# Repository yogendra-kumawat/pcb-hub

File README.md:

# PCB Hub

A curated collection of custom PCBs designed in **KiCad**, spanning embedded systems, motion control, RF communication, and analog signal generation. Each board was designed from scratch — schematic capture, layout, and fabrication-ready Gerbers — with a focus on clean routing, proper power distribution, and real-world hardware integration.

---

## Projects

| Project | Description | Board Size | Layers |
|---|---|---|---|
| [Flight Controller](#flight-controller) | STM32 + LoRa + IMU flight controller | 91.4 × 69.4 mm | 2 |
| [Function Generator](#function-generator) | STM32-based multi-waveform signal generator | 90.4 × 45.0 mm | 2 |
| [Writing Machine](#writing-machine) | 2-DOF polar arm plotter motor driver board | 56.2 × 26.0 mm | 2 |

## Machines
|Item|Description|
|---|---|
| [Drill Machine](#drill-machine) | Speed-controlled PCB drill with motor driver 
| [Solution Machine](#solution-machine) | Automated liquid dispensing controller 

---

## Tools

- **EDA**: KiCad 10.0
- **Fabrication**: JLCPCB / standard 2-layer FR4, 1.6 mm
- **Design Rules**: 0.2 mm min trace, 0.2 mm min clearance

---

*All KiCad source files (`.kicad_pcb` + `.kicad_sch`) are included in each project's `/kicad` subfolder.*

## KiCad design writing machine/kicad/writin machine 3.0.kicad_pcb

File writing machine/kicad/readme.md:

# KiCad Source — Writing Machine v3.0

This folder contains the complete KiCad project for the writing machine motor driver board.

## Files

| File | Description |
|---|---|
| `writin machine 3.0.kicad_sch` | Full schematic — STC8G1K08A MCU, 3× 2N2219 BJT motor drivers, AMS1117-5.0, UART header, motor output connectors |
| `writin machine 3.0.kicad_pcb` | 2-layer PCB layout — 56.2 × 26.0 mm, FR4 1.6 mm |

## Requirements

- KiCad **10.0** or later
- Custom symbol: `MCU_STC:STC8G1K08A-36I-DFN8` — included in the schematic's embedded library

## Design Notes

- Board thickness: **1.6 mm**

## How to Open

```bash
kicad "writin machine 3.0.kicad_pcb"
kicad "writin machine 3.0.kicad_sch"
```

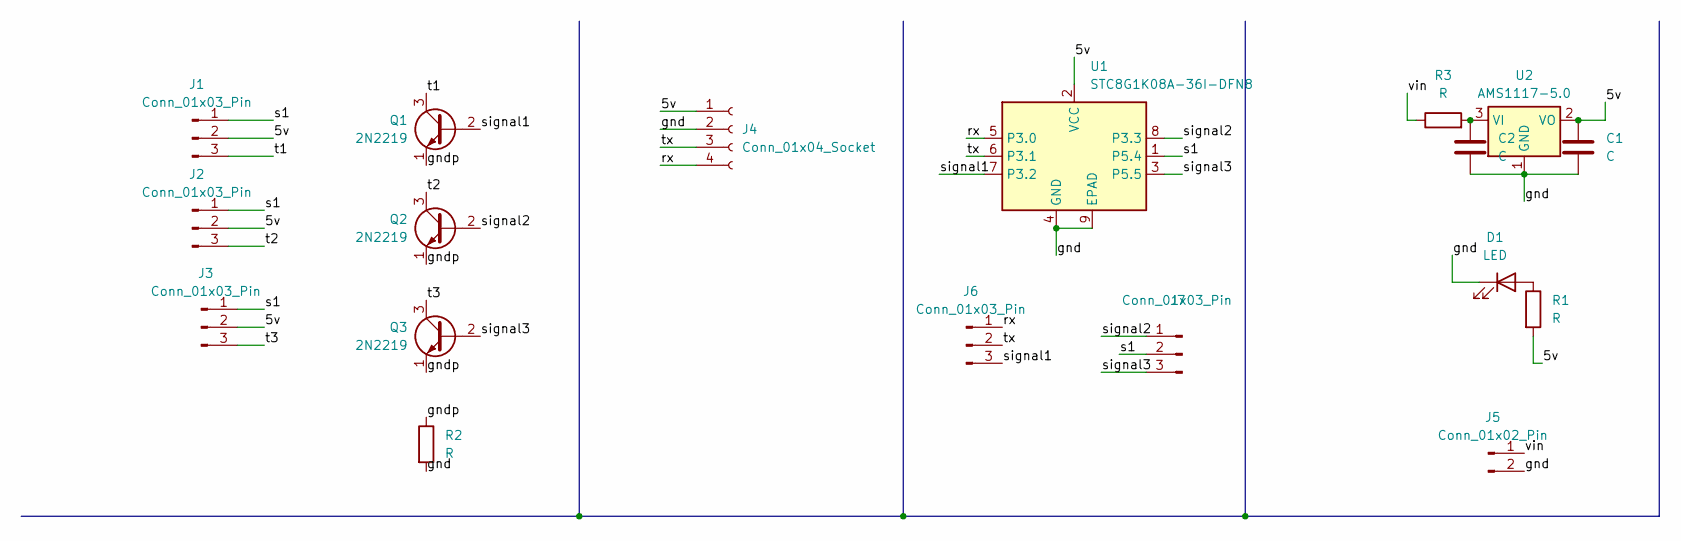
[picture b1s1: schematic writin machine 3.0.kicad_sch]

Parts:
C1, C2: C; C_Radial_D4.0mm_H5.0mm_P1.50mm
D1: LED; LED_D5.0mm
J1, J2, J3, J6, J7: Conn_01x03_Pin; PinSocket_1x03_P2.54mm_Vertical
J4: Conn_01x04_Socket; PinSocket_1x04_P2.54mm_Vertical
J5: Conn_01x02_Pin; PinHeader_1x02_P2.54mm_Vertical
Q1, Q2, Q3: 2N2219; TO-92
R1, R2, R3: R; R_Axial_DIN0204_L3.6mm_D1.6mm_P7.62mm_Horizontal
U1: STC8G1K08A-36I-DFN8; DFN-8-1EP_3x3mm_P0.5mm_EP1.7x2.4mm
U2: AMS1117-5.0; SOT-223-3_TabPin2

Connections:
/5v: C1.1, J1.2, J2.2, J3.2, J4.1, R1.2, U1.2 (VCC), U2.2 (VO)
/gnd: C1.2, C2.2, D1.1 (K), J4.2, J5.2, R2.2, U1.4 (GND), U1.9 (EPAD), U2.1 (GND)
/gndp: Q1.1 (E), Q2.1 (E), Q3.1 (E), R2.1
/rx: J4.4, J6.1, U1.5 (P3.0)
/s1: J1.1, J2.1, J3.1, J7.2, U1.1 (P5.4)
/signal1: J6.3, Q1.2 (B), U1.7 (P3.2)
/signal2: J7.1, Q2.2 (B), U1.8 (P3.3)
/signal3: J7.3, Q3.2 (B), U1.3 (P5.5)
/t1: J1.3, Q1.3 (C)
/t2: J2.3, Q2.3 (C)
/t3: J3.3, Q3.3 (C)
/tx: J4.3, J6.2, U1.6 (P3.1)
/vin: J5.1, R3.1
unnamed: D1.2 (A), R1.1
unnamed: C2.1, R3.2, U2.3 (VI)

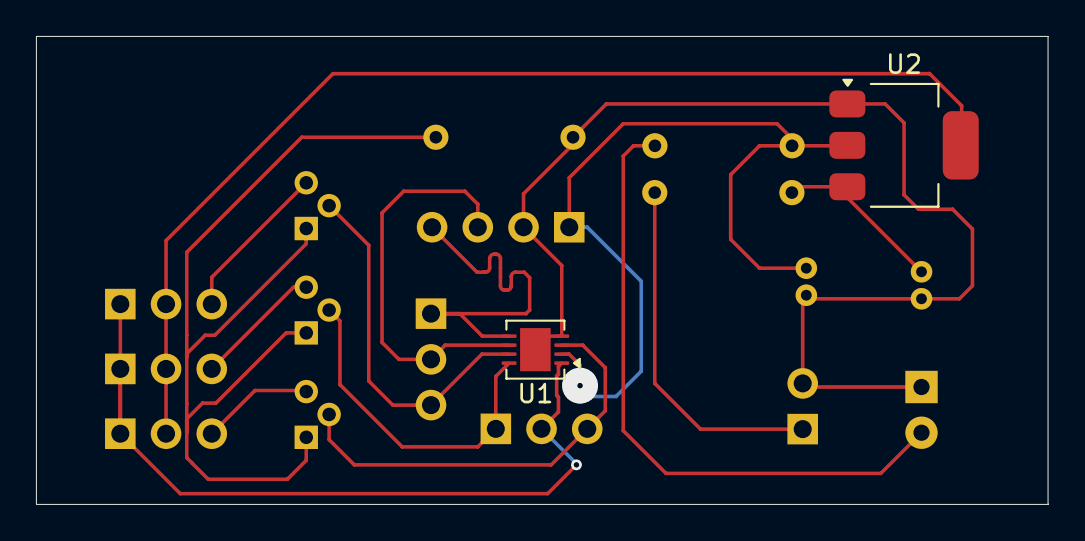
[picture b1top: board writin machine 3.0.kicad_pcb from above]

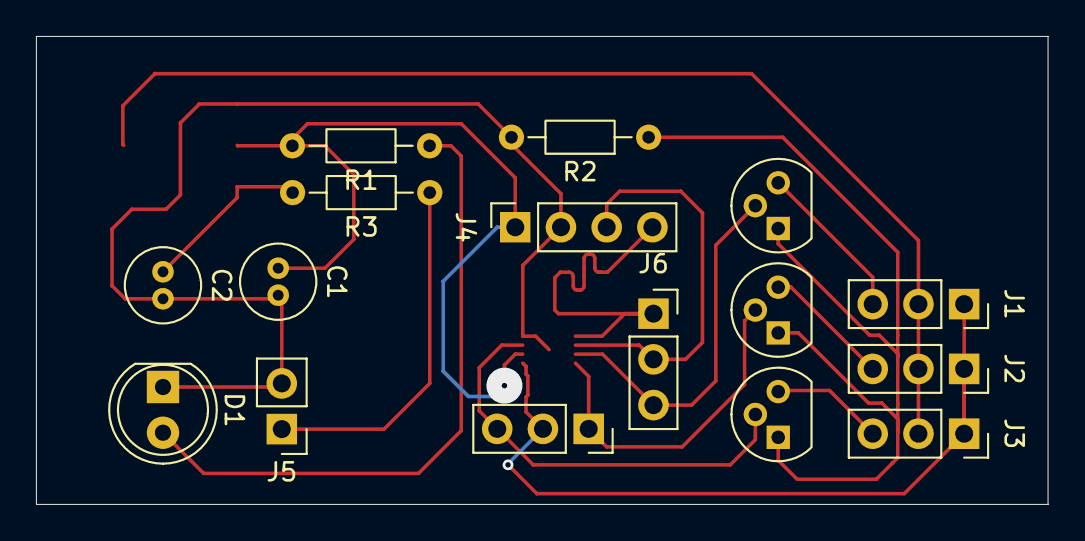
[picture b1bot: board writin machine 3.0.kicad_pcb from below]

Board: 2 copper layers, 56.2 x 26.0 mm, 18 parts (16 on the bottom side), 15 nets.

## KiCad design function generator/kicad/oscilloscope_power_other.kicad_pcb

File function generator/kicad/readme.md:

# KiCad Source — Function Generator

This folder contains the complete KiCad project for the function generator PCB.

## Files

| File | Description |
|---|---|
| `oscilloscope_power_other.kicad_sch` | Full schematic — STM32, AMS1117-3.3/5.0/ADJ regulators, 1N4007, OLED header, switches, potentiometers, barrel jack |
| `oscilloscope_power_other.kicad_pcb` | 2-layer PCB layout — 90.4 × 45.0 mm, FR4 1.6 mm |

## Requirements

- KiCad **10.0** or later
- All symbols from KiCad standard libraries (`Device`, `Connector`, `Regulator_Linear`, `Diode`, `Switch`)

## Design Notes

- Board thickness: **1.6 mm**
- Copper layers: **F.Cu** (top) and **B.Cu** (bottom)
- The schematic file name reflects the board's original dual purpose — function generator + oscilloscope port — from early planning

## How to Open

```bash
kicad oscilloscope_power_other.kicad_pcb
kicad oscilloscope_power_other.kicad_sch
```

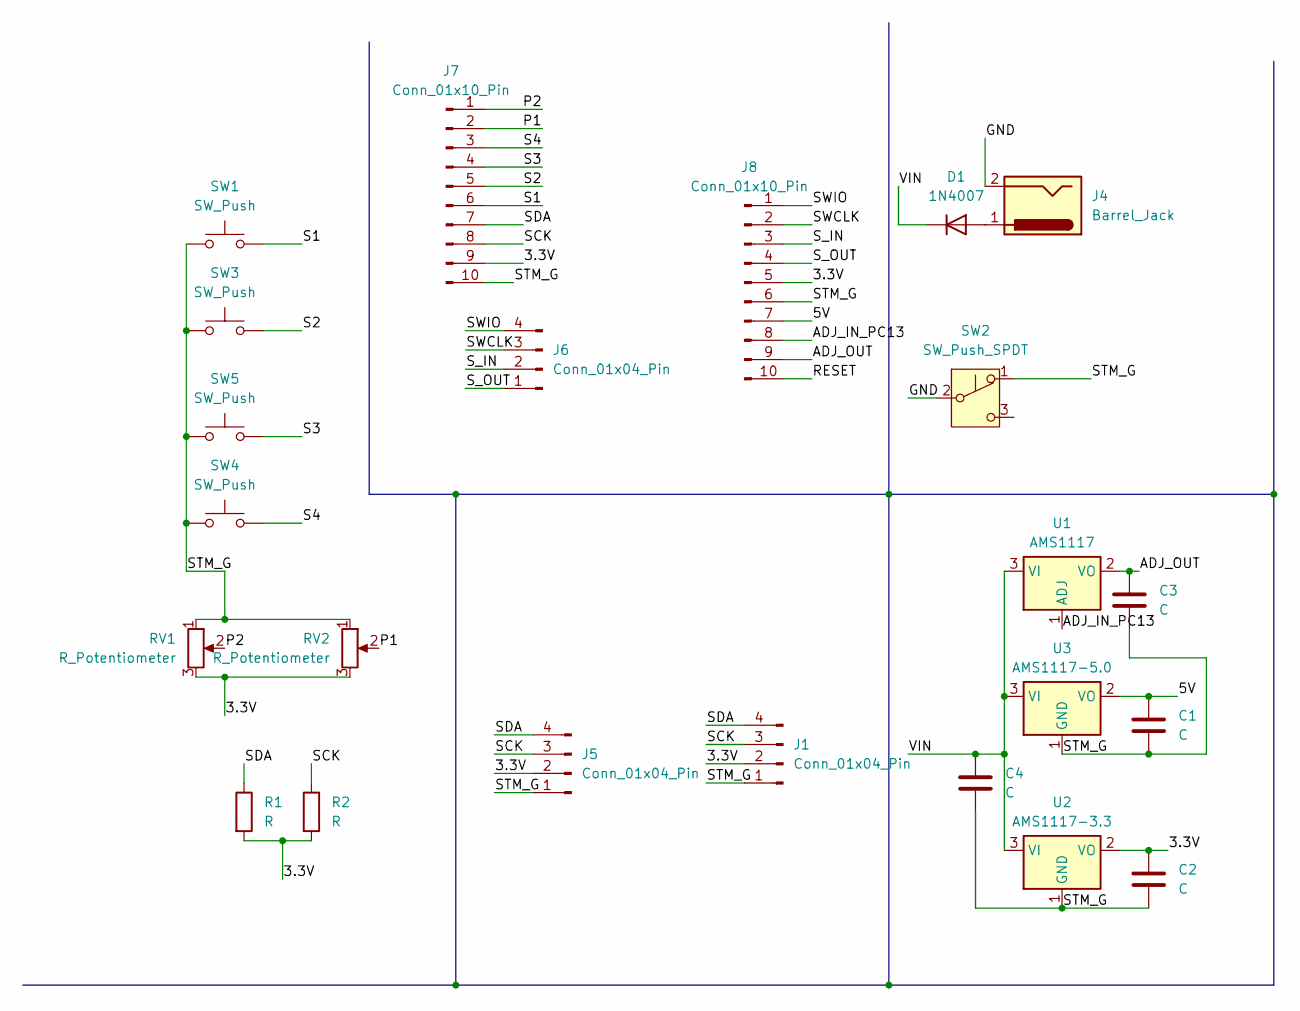
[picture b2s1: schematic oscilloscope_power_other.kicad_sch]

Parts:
C1, C2, C3, C4: C; C_Radial_D6.3mm_H11.0mm_P2.50mm
D1: 1N4007; D_DO-41_SOD81_P10.16mm_Horizontal
J1, J5, J6: Conn_01x04_Pin; JST_PH_B4B-PH-K_1x04_P2.00mm_Vertical
J4: Barrel_Jack; BarrelJack_SwitchcraftConxall_RAPC10U_Horizontal
J7, J8: Conn_01x10_Pin; PinHeader_1x10_P2.00mm_Vertical
R1, R2: R; R_Axial_DIN0204_L3.6mm_D1.6mm_P1.90mm_Vertical
RV1, RV2: R_Potentiometer; Potentiometer_Vishay_T73YP_Vertical
SW1, SW3, SW4, SW5: SW_Push; SW_PUSH_6mm
SW2: SW_Push_SPDT
U1: AMS1117; SOT-223-3_TabPin2
U2: AMS1117-3.3; SOT-223-3_TabPin2
U3: AMS1117-5.0; SOT-223-3_TabPin2

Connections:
/3.3V: C2.1, J1.2, J5.2, J7.9, J8.5, R1.2, R2.2, RV1.3, RV2.3, U2.2 (VO)
/5V: C1.1, J8.7, U3.2 (VO)
/ADJ_IN_PC13: J8.8, U1.1 (ADJ)
/ADJ_OUT: C3.1, J8.9, U1.2 (VO)
/GND: J4.2, SW2.2 (B)
/P1: J7.2, RV2.2
/P2: J7.1, RV1.2
/RESET: J8.10
/S1: J7.6, SW1.2
/S2: J7.5, SW3.2
/S3: J7.4, SW5.2
/S4: J7.3, SW4.2
/SCK: J1.3, J5.3, J7.8, R2.1
/SDA: J1.4, J5.4, J7.7, R1.1
/STM_G: C1.2, C2.2, C3.2, C4.2, J1.1, J5.1, J7.10, J8.6, RV1.1, RV2.1, SW1.1, SW2.1 (A), SW3.1, SW4.1, SW5.1, U2.1 (GND), U3.1 (GND)
/SWCLK: J6.3, J8.2
/SWIO: J6.4, J8.1
/S_IN: J6.2, J8.3
/S_OUT: J6.1, J8.4
/VIN: C4.1, D1.1 (K), U1.3 (VI), U2.3 (VI), U3.3 (VI)
unnamed: D1.2 (A), J4.1

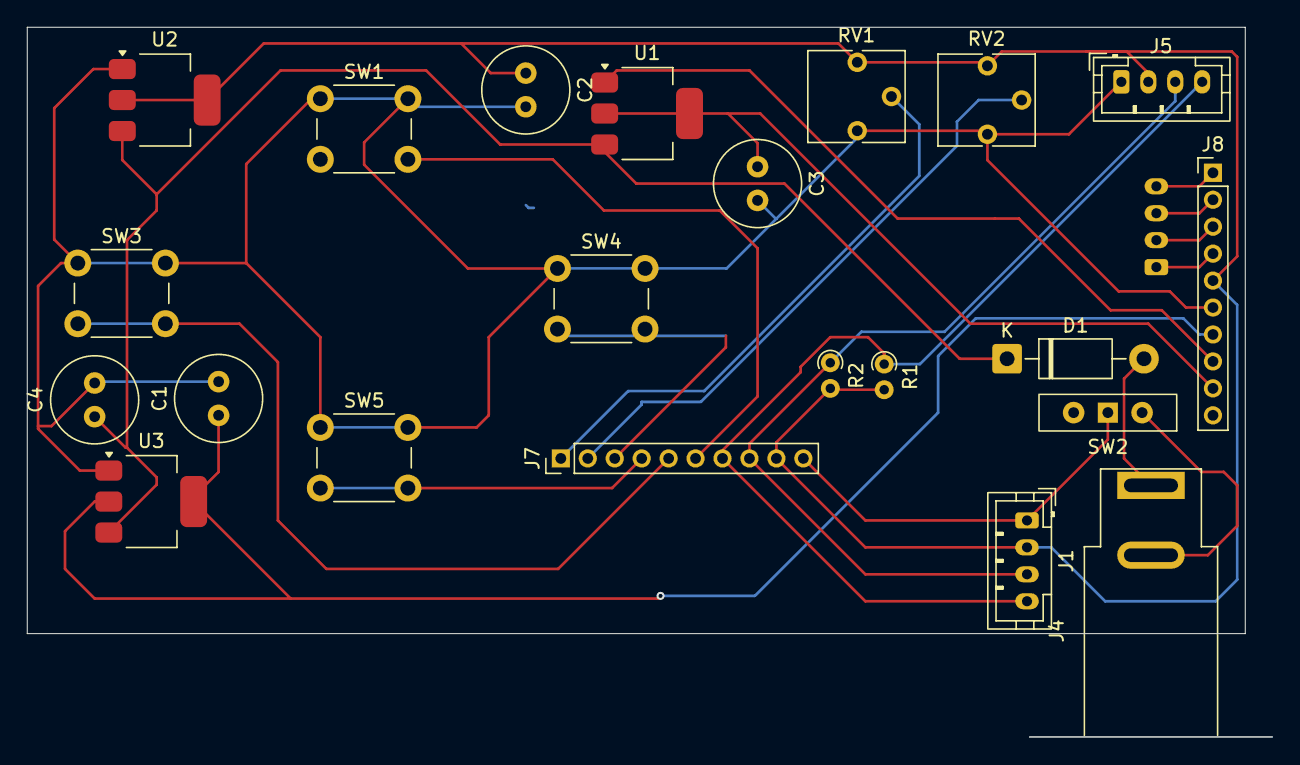
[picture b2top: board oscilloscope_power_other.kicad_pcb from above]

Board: 2 copper layers, 90.4 x 45.0 mm, 23 parts (1 on the bottom side), 20 nets.

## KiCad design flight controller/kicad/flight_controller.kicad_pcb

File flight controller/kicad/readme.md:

# KiCad Source — Flight Controller

This folder contains the complete KiCad project for the flight controller PCB.

## Files

| File | Description |
|---|---|
| `flight_controller.kicad_sch` | Full schematic — STM32F, Ra-01 LoRa, AMS1117-3.3/5.0 regulators, IMU header, servo outputs |
| `flight_controller.kicad_pcb` | 2-layer PCB layout — 91.4 × 69.4 mm, FR4 1.6 mm |

## Requirements

- KiCad **10.0** or later
- All symbols and footprints used are from the KiCad standard library or bundled custom symbols

## Design Notes

- Board thickness: **1.6 mm**
- Copper layers: **F.Cu** (components + signal) and **B.Cu** (ground pour + power traces)
- Paper size: **A4**

## How to Open

```bash
# Open the PCB layout
kicad flight_controller.kicad_pcb

# Open the schematic
kicad flight_controller.kicad_sch
```

Or launch KiCad and open either file from **File → Open**.

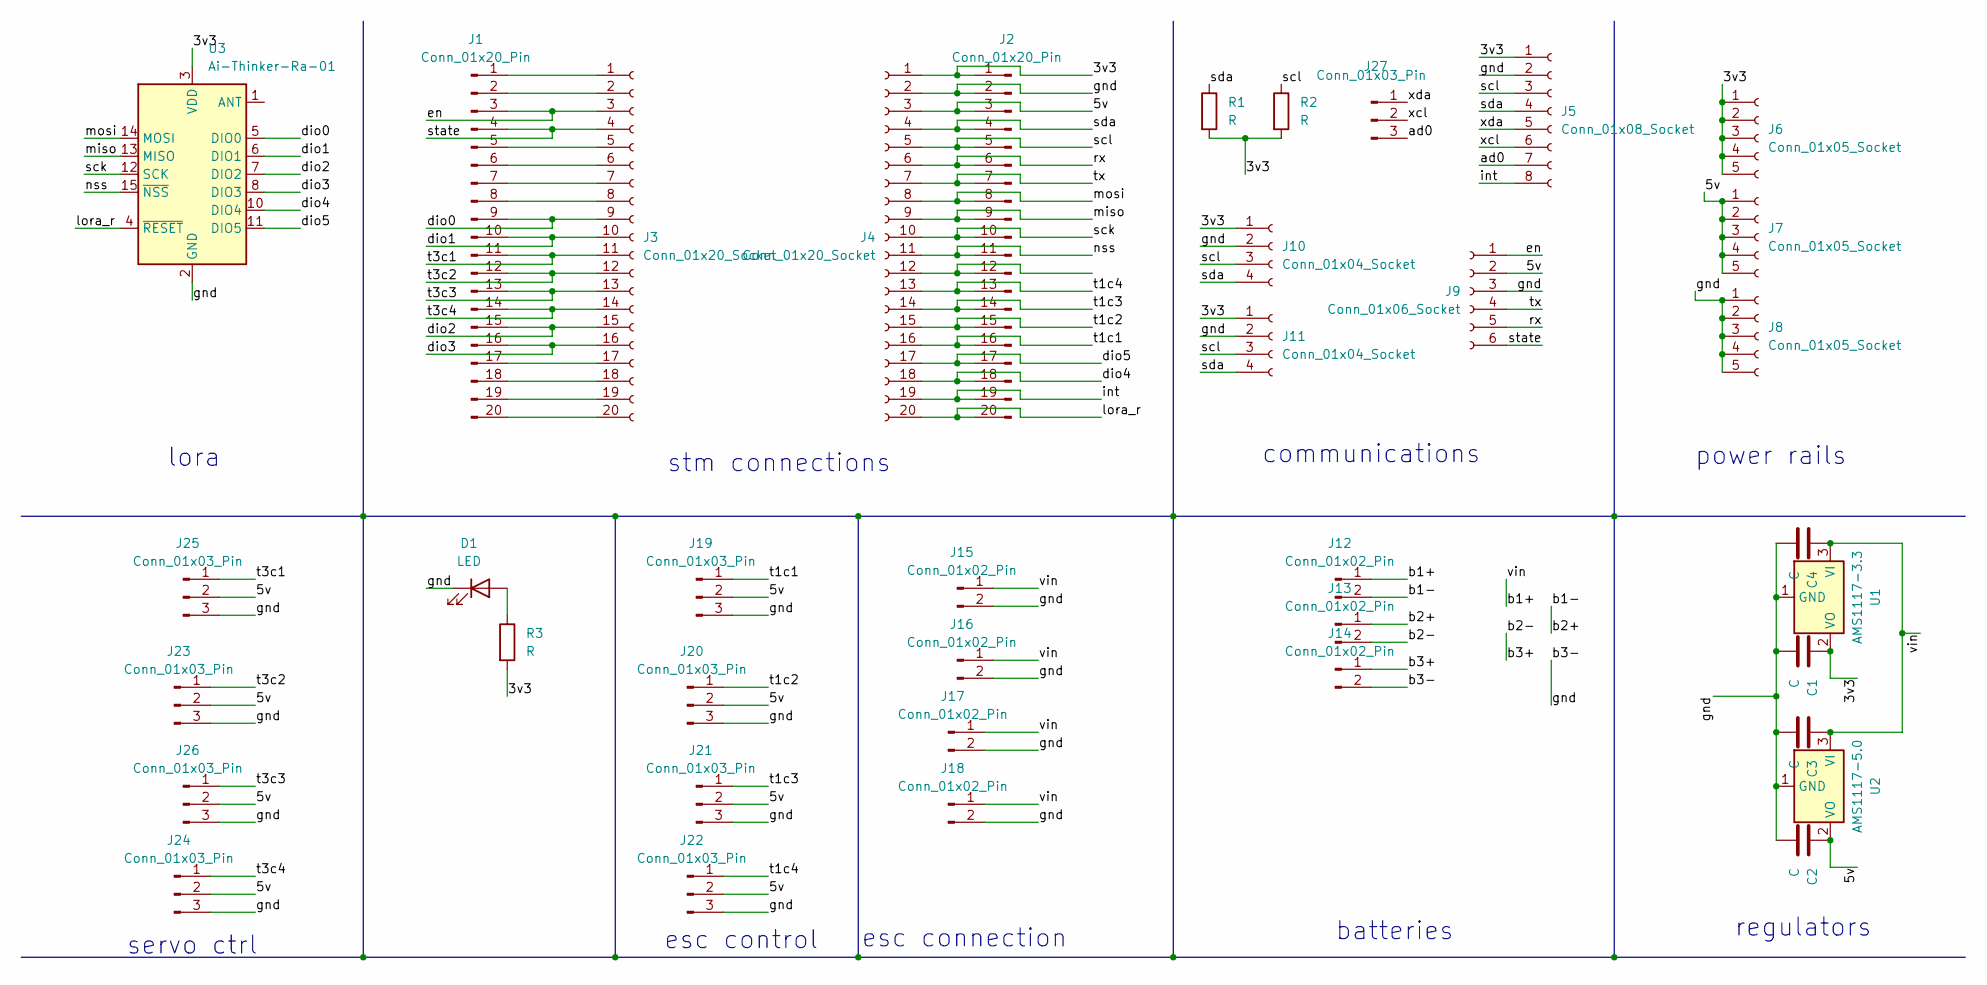
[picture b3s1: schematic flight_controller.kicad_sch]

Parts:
C1, C2, C3, C4: C; C_Disc_D3.0mm_W1.6mm_P2.50mm
D1: LED; LED_D3.0mm
J1, J2: Conn_01x20_Pin; PinSocket_1x20_P2.54mm_Vertical
J3, J4: Conn_01x20_Socket; PinSocket_1x20_P2.54mm_Vertical
J5: Conn_01x08_Socket; PinSocket_1x08_P2.54mm_Vertical
J6, J7, J8: Conn_01x05_Socket; PinSocket_1x05_P2.54mm_Vertical
J9: Conn_01x06_Socket; PinSocket_1x06_P2.54mm_Vertical
J10, J11: Conn_01x04_Socket; PinHeader_1x04_P2.54mm_Vertical
J12, J13, J14, J15, J16, J17, J18: Conn_01x02_Pin; PinHeader_1x02_P2.54mm_Vertical
J19, J20, J21, J22, J23, J24, J25, J26, J27: Conn_01x03_Pin; PinHeader_1x03_P2.54mm_Vertical
R1, R2, R3: R; R_Axial_DIN0207_L6.3mm_D2.5mm_P5.08mm_Vertical
U1: AMS1117-3.3; SOT-223-3_TabPin2
U2: AMS1117-5.0; SOT-223-3_TabPin2
U3: Ai-Thinker-Ra-01; Ai-Thinker-Ra-01-LoRa

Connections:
/3v3: C1.1, J2.1, J4.1, J5.1, J6.1, J6.2, J6.3, J6.4, J6.5, J10.1, J11.1, R1.2, R2.2, R3.2, U1.2 (VO), U3.3 (VDD)
/5v: C2.1, J2.3, J4.3, J7.1, J7.2, J7.3, J7.4, J7.5, J9.2, J19.2, J20.2, J21.2, J22.2, J23.2, J24.2, J25.2, J26.2, U2.2 (VO)
/ad0: J5.7, J27.3
/b1+: C3.1, C4.1, J12.1, J15.1, J16.1, J17.1, J18.1, U1.3 (VI), U2.3 (VI)
/b1-: J12.2, J13.1
/b2-: J13.2, J14.1
/b3-: C1.2, C2.2, C3.2, C4.2, D1.1 (K), J2.2, J4.2, J5.2, J8.1, J8.2, J8.3, J8.4, J8.5, J9.3, J10.2, J11.2, J14.2, J15.2, J16.2, J17.2, J18.2, J19.3, J20.3, J21.3, J22.3, J23.3, J24.3, J25.3, J26.3, U1.1 (GND), U2.1 (GND), U3.2 (GND), U3.9 (GND), U3.16 (GND)
/dio0: J1.9, J3.9, U3.5 (DIO0)
/dio1: J1.10, J3.10, U3.6 (DIO1)
/dio2: J1.15, J3.15, U3.7 (DIO2)
/dio3: J1.16, J3.16, U3.8 (DIO3)
/dio4: J2.18, J4.18, U3.10 (DIO4)
/dio5: J2.17, J4.17, U3.11 (DIO5)
/en: J1.3, J3.3, J9.1
/int: J2.19, J4.19, J5.8
/lora_r: J2.20, J4.20, U3.4 (~RESET)
/miso: J2.9, J4.9, U3.13 (MISO)
/mosi: J2.8, J4.8, U3.14 (MOSI)
/nss: J2.11, J4.11, U3.15 (~NSS)
/rx: J2.6, J4.6, J9.5
/sck: J2.10, J4.10, U3.12 (SCK)
/scl: J2.5, J4.5, J5.3, J10.3, J11.3, R2.1
/sda: J2.4, J4.4, J5.4, J10.4, J11.4, R1.1
/state: J1.4, J3.4, J9.6
/t1c1: J2.16, J4.16, J19.1
/t1c2: J2.15, J4.15, J20.1
/t1c3: J2.14, J4.14, J21.1
/t1c4: J2.13, J4.13, J22.1
/t3c1: J1.11, J3.11, J25.1
/t3c2: J1.12, J3.12, J23.1
/t3c3: J1.13, J3.13, J26.1
/t3c4: J1.14, J3.14, J24.1
/tx: J2.7, J4.7, J9.4
/xcl: J5.6, J27.2
/xda: J5.5, J27.1
unnamed: D1.2 (A), R3.1
unnamed: J1.1, J3.1
unnamed: J1.2, J3.2
unnamed: J1.5, J3.5
unnamed: J1.6, J3.6
unnamed: J1.7, J3.7
unnamed: J1.8, J3.8
unnamed: J1.17, J3.17
unnamed: J1.18, J3.18
unnamed: J1.19, J3.19
unnamed: J1.20, J3.20
unnamed: J2.12, J4.12

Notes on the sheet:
stm connections
batteries
servo ctrl
communications
lora
esc control
power rails
esc connection
regulators

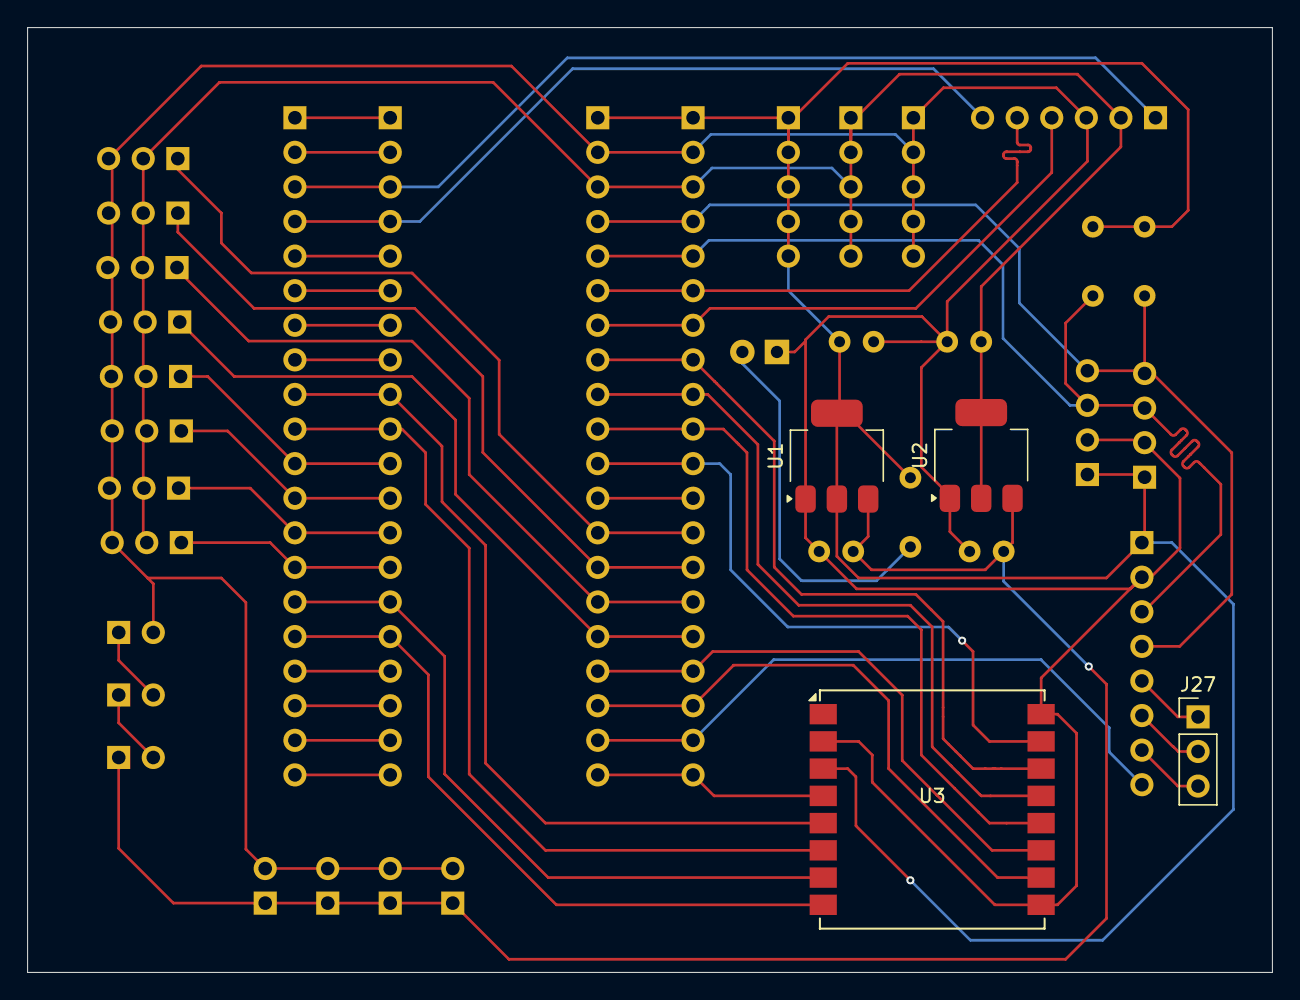
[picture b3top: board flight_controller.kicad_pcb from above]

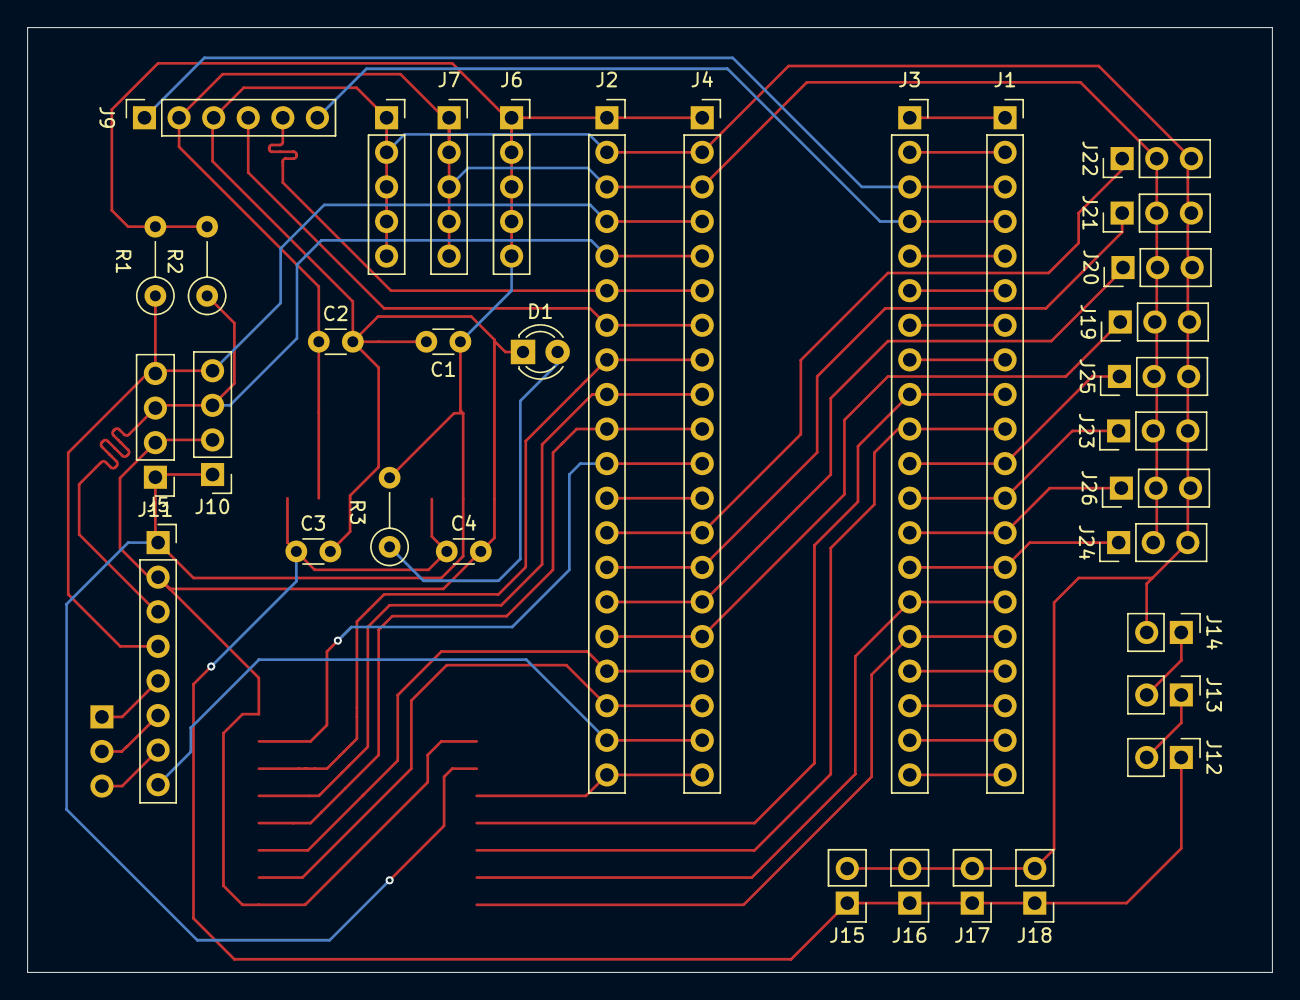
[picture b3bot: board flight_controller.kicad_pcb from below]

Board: 2 copper layers, 91.4 x 69.4 mm, 38 parts (34 on the bottom side), 47 nets.
